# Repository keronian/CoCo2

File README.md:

# CoCo2

This is my version of two separate composite video mod boards for the Tandy Color Computer 2, based initially on calphool's work.  One board is, like his, to replace a vertical RF Modulator, the other is to replace a horizontal RF Modulator.  The circuit design is the same for both.

I started with calphool's work, but re-did the whole board in KiCad.  The vertical board has some support PCBs that can be fabricated, and they serve as grounding points... You can use the board without them, but you'd need to use a grounding wire.  Horizontal board is mounted by taking a solder lug, bending the tab 90 degrees, and screwing it up into the board through the standoff (which should be soldered from the top for the best strength).

Grounding seems to work great so far, we'll see if I have issues with it backing out.  This is the first time I've tried doing anything with KiCad, so... hopefully it's not terrible.

With some advice from captainkirchoff in Discord, I've tweaked some resistors and added a circuit that let the channel select switch disable color.  Please note that this is really only for monochrome monitors, as it completely suppresses the chroma signal, which causes some weird artifacting in many color monitors.

Vertical version has also had a switch added to replicate the same functionality for that board... I used a SLW-1298856-5A-RA-N-D (will be in the BOM) - Had to import the footprint for it, so if you work on the board you'll need to grab that library from them.

Note that you can increase the value of the C4 capacitor and get better noise reduction (suggested value can go up to 10uF), but ceramic caps are still preferred.

The vertical board's support brackets are set up so that you can slip a thin metal tab (I cut a piece off of one of the solder lugs in the BOM) into the slot after it's slotted into the board, then you add solder to create the joint.

Overall fitment suggestion would be to solder the smaller supports to the back side of the board along with the headers (the size of header is VERY important, the BOM has the right size) - Then you slip it into place on the board with the longer supports just dry fit.. make sure everything is where you want it, then solder the longer supports into place, and finish by soldering the underside of the motherboard.  On mine, this resulted in a very solidly mounted board that would hardly wiggle.

https://www.digikey.com/en/mylists/list/GH709EISJW - This is the parts list for the board, with the updated transistors to make sure they were options that would be available and an audio jack that should fit the footprint I had on the board.

# Horizontal Board pics

# Vertical Board pics

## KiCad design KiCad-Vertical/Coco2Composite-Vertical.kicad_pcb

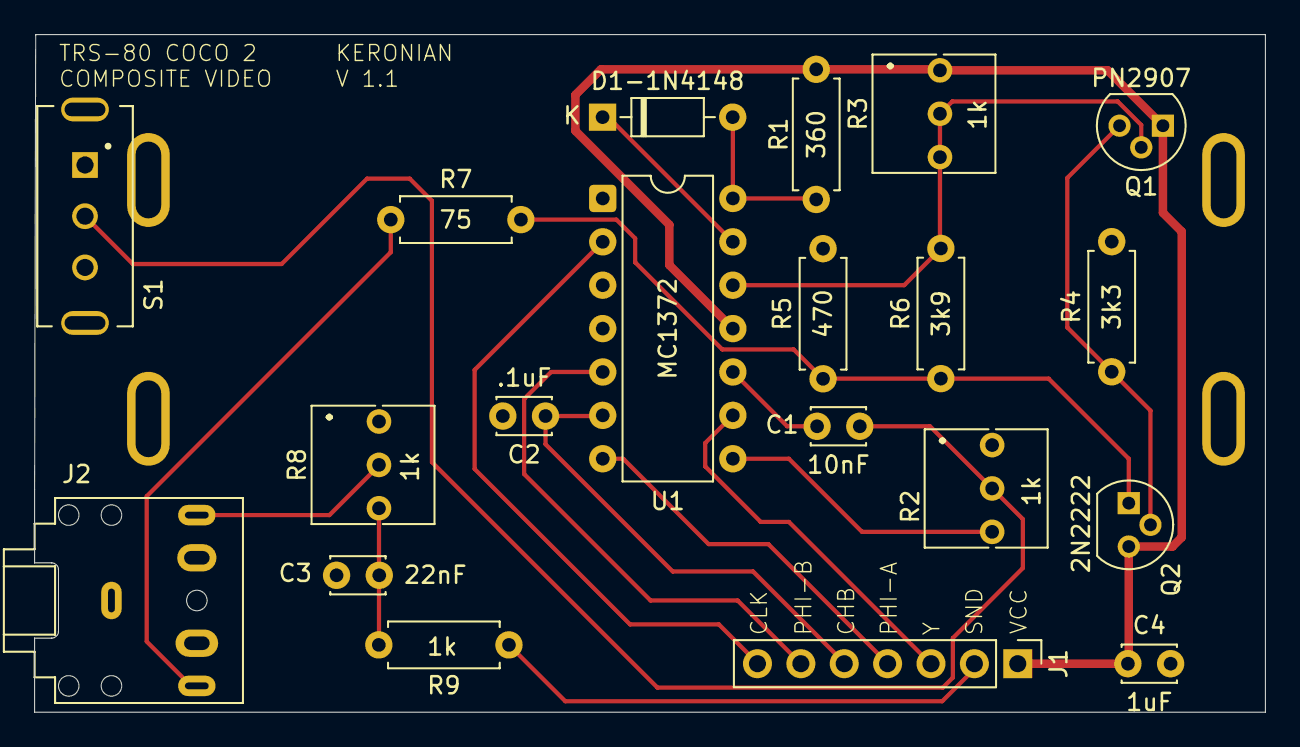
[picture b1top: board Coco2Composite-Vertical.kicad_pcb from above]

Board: 2 copper layers, 72.1 x 39.7 mm, 20 parts (0 on the bottom side), 19 nets.

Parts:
C1: 10nF; C_Disc_D3.0mm_W2.0mm_P2.50mm
C2: .1uF; C_Disc_D3.0mm_W2.0mm_P2.50mm
C3: 22nF; C_Disc_D3.0mm_W2.0mm_P2.50mm
C4: 1uF; C_Disc_D3.0mm_W2.0mm_P2.50mm
D1-1N4148: 1N4148; D_DO-35_SOD27_P7.62mm_Horizontal
J1: TO_COCO2; PinHeader_1x07_P2.54mm_Vertical
J2: AUDIO_JACK_3.5MM_KIT; Jack_3.5mm_CUI_SJ1-3525N_Horizontal
Q1: PN2907; TO-92
Q2: 2N2222; TO-92
R1: 360; R_Axial_DIN0207_L6.3mm_D2.5mm_P7.62mm_Horizontal
R2, R3, R8: 1k; Potentiometer_Bourns_3266Y_Vertical
R4: 3k3; R_Axial_DIN0207_L6.3mm_D2.5mm_P7.62mm_Horizontal
R5: 470; R_Axial_DIN0207_L6.3mm_D2.5mm_P7.62mm_Horizontal
R6: 3k9; R_Axial_DIN0207_L6.3mm_D2.5mm_P7.62mm_Horizontal
R7: 75; R_Axial_DIN0207_L6.3mm_D2.5mm_P7.62mm_Horizontal
R9: 1k; R_Axial_DIN0207_L6.3mm_D2.5mm_P7.62mm_Horizontal
S1: SLW-1298856-5A-RA-N-D; SW_SLW-1298856-5A-RA-N-D
U1: MC1372; DIP-14_W7.62mm

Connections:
/CHB: C2.1, J1.5, U1.6 (COL_REF_IN)
/CLK: J1.7, U1.2 (OSC_IN)
/COMP_OUT: J2.T, R7.1
/PHI-A: J1.4, U1.7 (COL_A_IN)
/PHI-B: J1.6, U1.5 (COL_B_IN)
/SND: J1.2, R9.1
/SND_OUT: J2.R, R8.2
/Y: J1.3, U1.9 (LUM_IN)
GND: C2.2, C3.2, C4.2, J2.S, R2.1, R4.2, R5.2, R8.1, S1.3, S1.SH1, S1.SH2, U1.4 (GND)
unnamed: C1.2, R2.2, S1.2
unnamed: C3.1, R8.3, R9.2
unnamed: D1-1N4148.2 (A), R1.2, U1.14 (RF_TANK_2)
unnamed: D1-1N4148.1 (K), U1.13 (RF_TANK_1)
unnamed: Q1.3, Q2.2 (B), R4.1
unnamed: Q2.1 (E), R5.1, R6.1, R7.2
unnamed: C1.1, U1.10 (CHROM_IN)
unnamed: R2.3, U1.8 (CHROM_MOD_OUT)
unnamed: Q1.2, R3.2, R3.3, R6.2, U1.12 (RF_OUT)
VCC: C4.1, J1.1, Q1.1, Q2.3 (C), R1.1, R3.1, U1.11 (VCC)

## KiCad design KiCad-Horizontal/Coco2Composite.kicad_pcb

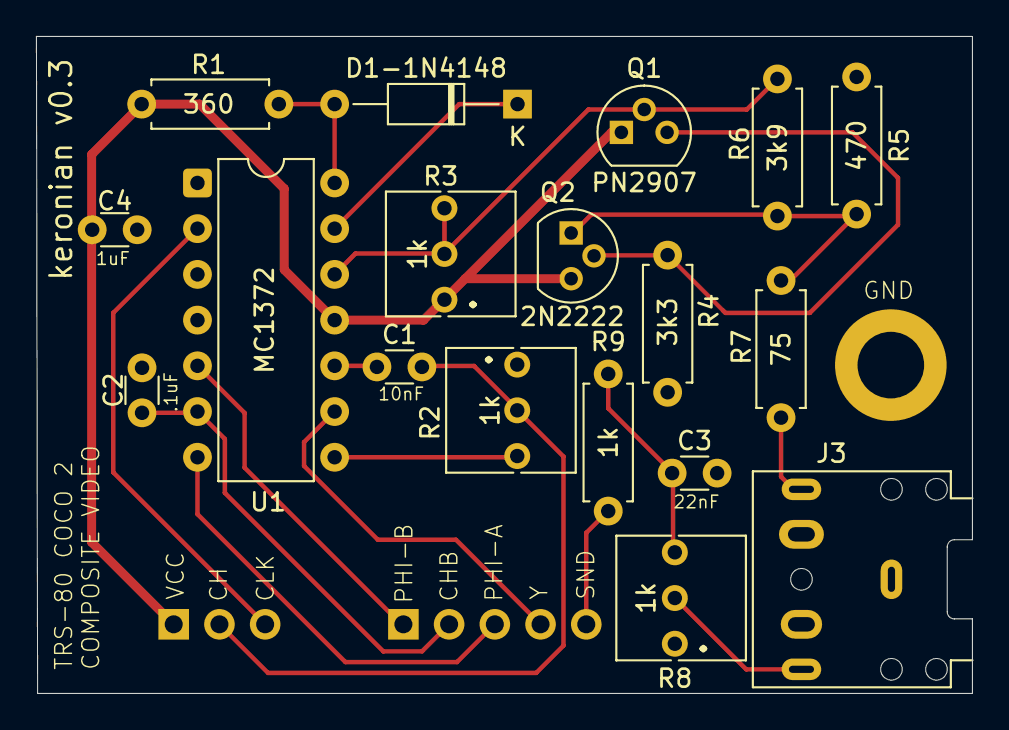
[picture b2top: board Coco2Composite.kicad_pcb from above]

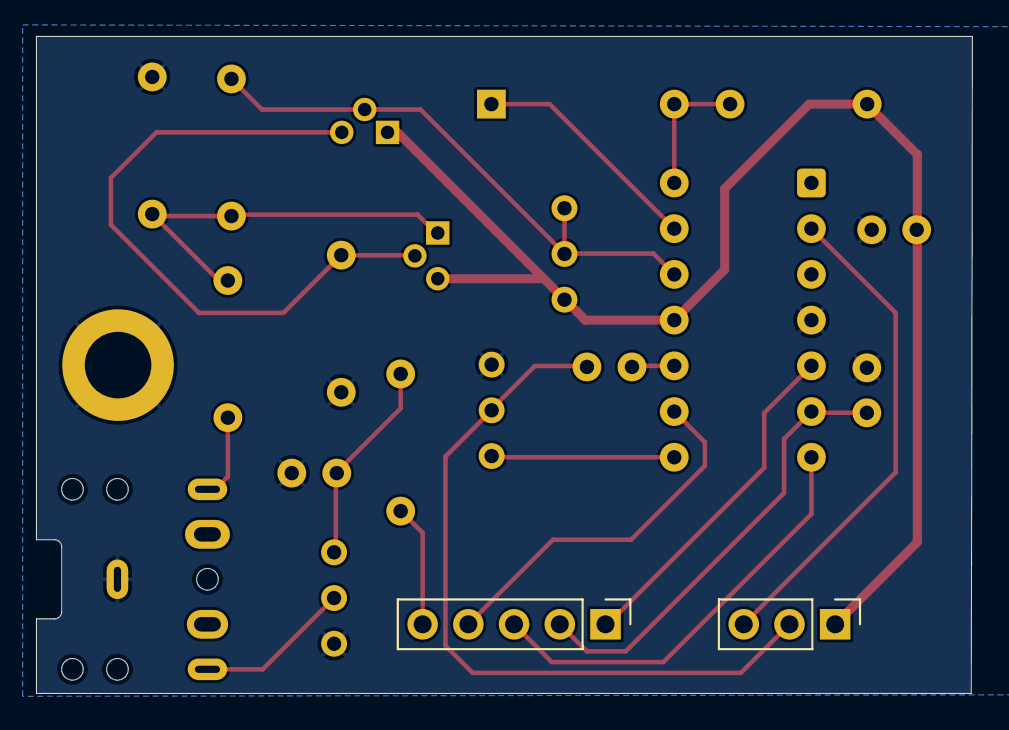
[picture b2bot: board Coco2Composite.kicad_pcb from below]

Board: 2 copper layers, 52.0 x 36.5 mm, 21 parts (2 on the bottom side), 19 nets.

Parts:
C1: 10nF; C_Disc_D3.0mm_W1.6mm_P2.50mm
C2: .1uF; C_Disc_D3.0mm_W1.6mm_P2.50mm
C3: 22nF; C_Disc_D3.0mm_W1.6mm_P2.50mm
C4: 1uF; C_Disc_D3.0mm_W1.6mm_P2.50mm
D1-1N4148: 1N4148; D_DO-35_SOD27_P10.16mm_Horizontal
J1: MA03-1; PinHeader_1x03_P2.54mm_Vertical
J2: MA05-1; PinHeader_1x05_P2.54mm_Vertical
J3: AUDIO_JACK_3.5MM_PTH; Jack_3.5mm_CUI_SJ1-3525N_Horizontal
PAD1: 2,54/0,8; MountingHole_3.7mm_Pad
Q1: PN2907; TO-92
Q2: 2N2222; TO-92
R1: 360; R_Axial_DIN0207_L6.3mm_D2.5mm_P7.62mm_Horizontal
R2, R3, R8: 1k; Potentiometer_Bourns_3266Y_Vertical
R4: 3k3; R_Axial_DIN0207_L6.3mm_D2.5mm_P7.62mm_Horizontal
R5: 470; R_Axial_DIN0207_L6.3mm_D2.5mm_P7.62mm_Horizontal
R6: 3k9; R_Axial_DIN0207_L6.3mm_D2.5mm_P7.62mm_Horizontal
R7: 75; R_Axial_DIN0207_L6.3mm_D2.5mm_P7.62mm_Horizontal
R9: 1k; R_Axial_DIN0207_L6.3mm_D2.5mm_P7.62mm_Horizontal
U1: MC1372; DIP-14_W7.62mm

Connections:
/CH: C1.2, J1.2, R2.2
/CHB: C2.1, J2.2, U1.6 (COL_REF_IN)
/CHROM_IN: C1.1, U1.10 (CHROM_IN)
/CHROM_MOD_OUT: R2.3, U1.8 (CHROM_MOD_OUT)
/CLK: J1.3, U1.2 (OSC_IN)
/COMP_OUT: J3.T, R7.2
/PHI-A: J2.3, U1.7 (COL_A_IN)
/PHI-B: J2.1, U1.5 (COL_B_IN)
/Q1_E: Q1.3, Q2.2 (B), R4.2
/Q2_E: Q2.1 (E), R5.2, R6.2, R7.1
/RF_OUT: Q1.2, R3.2, R3.3, R6.1, U1.12 (RF_OUT)
/RF_TANK_1: D1-1N4148.1, U1.13 (RF_TANK_1)
/RF_TANK_2: D1-1N4148.2, R1.1, U1.14 (RF_TANK_2)
/SND: J2.5, R9.2
/SND_OUT: J3.R, R8.2
/SND_OUT_RES: C3.1, R8.3, R9.1
/Y: J2.4, U1.9 (LUM_IN)
GND: C2.2, C3.2, C4.2, J3.S, PAD1.1, R2.1, R4.1, R5.1, R8.1, U1.4 (GND)
VCC: C4.1, J1.1, Q1.1, Q2.3 (C), R1.2, R3.1, U1.11 (VCC)

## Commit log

2025-07-23 Tried making a version for the horizontal RF mod
2025-07-23 Readme update
2025-07-25 Added KiCad and digikey parts list
2025-07-26 Updated KiCad based on board schematic
2025-07-26 Removed the EAGLE version as it's not really useful at this point
2025-07-26 updated layout, shifted headers a tiny bit
2025-07-26 updated layout to try to simplify routes
2025-07-26 simplified layout & added username
2025-07-26 updated labels
2025-07-26 fixed missing ground connection on audio jack
2025-07-26 fixed missing VCC connection on R3
2025-07-28 moved ground pad to hopefully have it work as a support strut anchor point
2025-07-28 Minor tweaks
2025-07-29 Added gerbers that I sent off to be manufactured for testing
2025-08-06 Moved KiCad files to KiCad-Horizontal directory, added KiCad for the vertical entry using the 3.5mm jack
2025-08-06 Fixed a missed ground in the vertical board
2025-08-06 realized I missed some ground and vcc pins
2025-08-06 Added info to the readme
2025-08-06 Modified the silkscreen on the vertical board to make it easier to know where things go
2025-08-06 Updated the vertical model to let the resistors lie down on the board, kept the old one in case someone wants the board the same way it was
2025-08-08 removed a pointless trace
2025-08-08 Increased the footprint for the resistors since the one I picked was still too small
2025-08-08 minor updates to the vertical PCB to clean up trace paths
2025-08-08 removed the gerbers for the smaller resistor footprint
2025-08-14 Moved the audio jack over a little to make it a bit better centered
2025-08-14 added a picture of the finished board with an image of the lug mount
2025-08-15 Big changes to let the channel select switch disable color
2025-08-15 increased the footprint of the variable resistors to match what I have in the BOM, added a dot for orientation, switched schematic symbols to something more standard
2025-08-15 Changed diode footprint for smaller diode
2025-08-15 Reworked traces to keep them all on the front, shrunk trace width to 0.25
2025-08-15 Added a supply bypass capacitor
2025-08-15 Added a note about C4
2025-08-16 Overhauled vertical board based on lessons learned working on horizontal board
2025-08-16 Fixed label on diode
2025-08-16 Fixed the bypass cap on the schematic
2025-08-16 Updated some schematic symbols and rerouted a few things on the vertical board
2025-08-18 Added color switch to vertical board
2025-08-18 shifted the labels on J1 up to match the move of the header
2025-08-18 Fixed associations and made cap value visible for vert board
2025-08-21 fixed the board outline to be more consistent so you can export STEP files and such
2025-09-16 Added supports for vertical board
2025-09-29 Updated vertical board based on header selection and switch positioning, added pictures of horizontal board
2025-09-29 Header for pics
2025-10-05 Added vertical board pics
2025-10-05 Updated documentation a bit
2025-10-07 Fixed formatting for header
